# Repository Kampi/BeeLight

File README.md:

# BeeLight - Zigbee based light & environment sensor for Home Automation

## Table of Contents

- [BeeLight - Zigbee based light \& environment sensor for Home Automation](#beelight---zigbee-based-light--environment-sensor-for-home-automation)
  - [Table of Contents](#table-of-contents)
  - [About](#about)
    - [Technical features](#technical-features)
  - [Before you start](#before-you-start)
    - [PCB](#pcb)
    - [Firmware](#firmware)
      - [Build the firmware](#build-the-firmware)
      - [Flash the firmware](#flash-the-firmware)
      - [Generate the production config for the device](#generate-the-production-config-for-the-device)
        - [Using west](#using-west)
        - [Using the command line](#using-the-command-line)
    - [Housing](#housing)
    - [Zigbee](#zigbee)
      - [Standard clusters](#standard-clusters)
      - [Custom cluster](#custom-cluster)
      - [Zigbee Dongle](#zigbee-dongle)
      - [Install the device to Zigbee2MQTT](#install-the-device-to-zigbee2mqtt)
      - [Using the NCS Zigbee Shell](#using-the-ncs-zigbee-shell)
  - [Directory structure](#directory-structure)
  - [Resources](#resources)
  - [Maintainer](#maintainer)

## About

Open-Source Zigbee-based light and environmental sensor with [Zigbee2MQTT](https://www.zigbee2mqtt.io/) support for your Home Automation (e.g., Home Assistant).

### Technical features

- Cutting-edge MCU module with an nRF54L, running Zephyr
- Powered by a single coin cell
- Can measure
  - Temperature
  - Humidity
  - Pressure
  - IAQ
  - CO2 equivalent
  - VOC equivalent
  - Light intensity
  - Battery voltage
- Small housing (40x42x20 mm)
- Very basic electronic → Can be assembled by hand very easily
- Zigbee2MQTT compatibility

## Before you start

The project directory contains the hardware as a [KiCad 9](https://www.kicad.org/download/) project, the firmware and the Zigbee2MQTT configuration. You can check it out with Git:

```sh
git clone https://github.com/Kampi/BeeLight
cd BeeLight
git submodule update --init --recursive
cd firmware/app
west init -l .
west update
```

You also need [nrfutil](https://www.nordicsemi.com/Products/Development-tools/nRF-Util) and the `nrf5sdk-tools` to flash the production configuration to the sensor. First install `nrfutil` and then run the following command to install the SDK tools:

```sh
nrfutil install nrf5sdk-tools
```

### PCB

The project uses [Kibot](https://github.com/INTI-CMNB/KiBot) to automatically generate all required output data. After installing it you can execute the following command to run it:

```sh
cd hardware
./kibot-launch.sh
```

As an alternative you can run it via CI/CD in GitHub.

> **NOTE**
> You have to provide a Mouser API key with a variable called `MOUSER_KEY` to make use of the KiCost feature in the Kibot job.
>
> **NOTE**
> The programming connector is optional and can be left out or unsoldered after flashing the device.

### Firmware

#### Build the firmware

The firmware can be built with the following command:

```sh
cd firmware/app
west build --build-dir build . --pristine --board beelight@1/nrf54l15/cpuapp -- -DNCS_TOOLCHAIN_VERSION=NONE -DEXTRA_CONF_FILE=config/debug.conf -DBOARD_ROOT=.
```

You also need a Zigbee network to test and integrate the device. I use [Zigbee2MQTT](https://www.zigbee2mqtt.io/) running on a Raspberry Pi which allows me to connect my Zigbee network with my Home Automation.

> **NOTE**
> I do not support other Zigbee networks (like [ZHA](https://www.home-assistant.io/integrations/zha/)). The Zigbee standard allows you to connect the device with all other networks but I can't deliver a functional integration for these networks. You have to do it on your own!

#### Flash the firmware

After building the firmware you can run

```sh
west flash
```

to flash the firmware into the module.

> **NOTE**
> For some reason the current consumption stays high after flashing. I recommend a complete power cycle after flashing to make sure the device is consuming the lowest current possible.

#### Generate the production config for the device

##### Using west

You can run the command `west upload_config` to build and upload your configuration to the device automatically.

##### Using the command line

You must flash a production config to the device, before you can use it with Zigbee. You can either use the prebuilt config from the project or adjust it according to your needs.

```sh
nrfutil nrf5sdk-tools zigbee production_config zigbee_config.yml zigbee_config.hex --offset 0x17a000
nrfjprog --program zigbee_config.hex --verify
```

> **NOTE**
> The offset `0x17a000` is taken from the `PM_ZBOSS_PRODUCT_CONFIG_OFFSET` macro in `build/<app>/zephyr/include/generated/pm_config.h`. Also make sure to change `extended_address` in the Zigbee
> configuration file if you use more than one device!

### Housing

The housing is optimized for 3D printing and needs ~12 g of filament (PLA). You can find all the needed files in the `3d-printing` directory of this project.

### Zigbee

The device uses different standard and custom cluster to report the data to the network.

#### Standard clusters

| Cluster | ID |
| ------- | -- |
| Temperature | 0x0402 |
| Pressure | 0x0403 |
| Rel. Humidity | 0x0405 |
| Light | 0x0400 |

#### Custom cluster

The device uses three custom cluster to report `IAQ`, `VOC` and `CO2` to the network. Both clusters have three attributes for `value`, `min_value`, `max_value` and `tolerance`.

| Cluster | ID |
| ------- | -- |
| IAQ | 0x1A0A |
| VOC | 0x1A0B |
| CO2 | 0x1A0C |

| Attribute | ID |
| --------- | -- |
| Value | 0x0000 |
| Min. Value | 0x0001 |
| Max. Value | 0x0002 |
| Tolerance | 0x0003 |

#### Zigbee Dongle

Make sure to use a Zigbee 3 compatible dongle like [SONOFF ZBDongle-E](https://sonoff.tech/product/gateway-and-sensors/sonoff-zigbee-3-0-usb-dongle-plus-e/) and update the firmware to the latest version to prevent issues. You can follow [this](https://dongle.sonoff.tech/sonoff-dongle-flasher/) guide if you use a SONOFF dongle.

#### Install the device to Zigbee2MQTT

> **NOTE**
> Because it's not possible to use custom clusters with Zigbee2MQTT easily, you must adjust the application directly to use the sensor. Please take a look into the directory `z2m/data/external_converters/example` if you want to check how the modified files look like.

1. Download and install [Zigbee2MQTT](https://github.com/zigbee2mqtt/hassio-zigbee2mqtt)
2. Copy the external converter from `z2m/data_external_converters` to the `data` directory of your `Zigbee2MQTT` installation
3. Switch into the directory `.../zigbee2mqtt/node_modules/zigbee-herdsman/dist/zspec/zcl/definition` and open `cluster.js` and add the following code to `exports.Clusters`

```ts
...
    msBeelightIAQ: {
        ID: 6666,
        attributes: {
            measuredValue: { ID: 0, type: enums_1.DataType.UINT16 },
            minMeasuredValue: { ID: 1, type: enums_1.DataType.UINT16 },
            maxMeasuredValue: { ID: 2, type: enums_1.DataType.UINT16 },
            tolerance: { ID: 3, type: enums_1.DataType.UINT8 },
        },
        commands: {},
        commandsResponse: {},
    },
    msBeelightVOC: {
        ID: 6667,
        attributes: {
            measuredValue: { ID: 0, type: enums_1.DataType.UINT16 },
            minMeasuredValue: { ID: 1, type: enums_1.DataType.UINT16 },
            maxMeasuredValue: { ID: 2, type: enums_1.DataType.UINT16 },
            tolerance: { ID: 3, type: enums_1.DataType.UINT8 },
        },
        commands: {},
        commandsResponse: {},
    },
    msBeelightCO2: {
        ID: 6668,
        attributes: {
            measuredValue: { ID: 0, type: enums_1.DataType.UINT16 },
            minMeasuredValue: { ID: 1, type: enums_1.DataType.UINT16 },
            maxMeasuredValue: { ID: 2, type: enums_1.DataType.UINT16 },
            tolerance: { ID: 3, type: enums_1.DataType.UINT8 },
        },
        commands: {},
        commandsResponse: {},
    },
...
```

4. Save the file
5. Switch to `.../zigbee2mqtt/node_modules/zigbee-herdsman-converters/dist/lib`
6. Open the file `modernExtend.js` and add the following cluster to the end of the list at the end of the file:
7. Add

```js
...
exports.BeeLight_iaq = BeeLight_iaq;
exports.BeeLight_co2 = BeeLight_co2;
exports.BeeLight_voc = BeeLight_voc;
...
```

8. Extend the following section

```js
// #region Measurement and Sensing
function BeeLight_iaq(args = {}) {
    return numeric({
        name: "BeeLight_iaq",
        cluster: "msBeelightIAQ",
        attribute: "measuredValue",
        reporting: { min: "5_MINUTES", max: "1_HOUR", change: 10 },
        description: "Measured IAQ value",
        unit: "",
        scale: 1,
        access: "STATE_GET",
        ...args,
    });
}
function BeeLight_co2(args = {}) {
    return numeric({
        name: "BeeLight_co2",
        cluster: "msBeelightCO2",
        attribute: "measuredValue",
        reporting: { min: "5_MINUTES", max: "1_HOUR", change: 10 },
        description: "Measured CO2 value",
        unit: "ppm",
        scale: 1,
        access: "STATE_GET",
        ...args,
    });
}
function BeeLight_voc(args = {}) {
    return numeric({
        name: "BeeLight_voc",
        cluster: "msBeelightVOC",
        attribute: "measuredValue",
        reporting: { min: "5_MINUTES", max: "1_HOUR", change: 10 },
        description: "Measured VOC value",
        unit: "ppm",
        scale: 1,
        access: "STATE_GET",
        ...args,
    });
}
...
```

9. Save the file
10. Restart Zigbee2MQTT

The device can now be connected to your Zigbee network and with this to your Home Assistant.

#### Using the NCS Zigbee Shell

You can test the device by using the NCS Zigbee Shell example and an nRF54DK or an nRF5340DK.

1. Flash the Zigbee Shell example to your board
2. Execute `nvram disable`
3. Execute `bdb role zc`
4. Execute `bdb channel 11`
5. Execute `bdb start`
6. Flash the sensor device firmware and the network configuration
7. Reset the sensor device and start the join procedure
8. You should get this output from the network coordinator device

```sh
[00:05:05.648,345] <inf> zigbee_app_utils: Joined network successfully (Extended PAN ID: f4ce36b2d4c06ca0, PAN ID: 0x6057)
[00:05:24.536,529] <inf> zigbee_app_utils: Device authorization event received (short: 0x02fa, long: 86d79ac5bae41fa3, authorization type: 3, authorization status: 0)
[00:05:24.536,773] <inf> zigbee_app_utils: Unimplemented signal (signal: 53, status: 0)
[00:05:24.537,139] <inf> zigbee_app_utils: Device update received (short: 0x02fa, long: 86d79ac5bae41fa3, status: 1)
```

9. Now you can read the clusters with `zcl attr read <Address> 10 <Cluster> 0x0104 0x0000`
10. Use `zcl subscribe on <Address> 10 <Cluster> 0x0104 0x00 33 <Min (s)> <Max (s)>` to create a binding for the given cluster

## Directory structure

- `3d-print`: All 3D print-related files
- `cad`: All relevant 3D models
- `docs`: All kinds of project documentation like schematics, BOM, etc.
  - `drawings`: 2D drawings for subcomponents, etc.
  - `images`: All documentation-relateBd images
- `hardware`: KiCad project for the PCB
- `firmware`: Zephyr project for the device firmware
- `prebuilt`: Prebuilt binaries
- `z2m`: Zigbee2MQTT-related files

## Resources

- [Adding new Zigbee2MQTT devices](https://www.zigbee2mqtt.io/advanced/support-new-devices/01_support_new_devices.html)
- [Zigbee Cluster Library Specification](https://zigbeealliance.org/wp-content/uploads/2019/12/07-5123-06-zigbee-cluster-library-specification.pdf)
- [Generating HEX files for Zigbee production configuration](https://docs.nordicsemi.com/bundle/nrfutil/page/nrfutil-nrf5sdk-tools/guides/generating_zigbee_hex.html)
- [Zigbee Converters](https://github.com/Koenkk/zigbee-herdsman-converters)
- [KiBot Template](https://github.com/nguyen-v/KDT_Hierarchical_KiBot)
- [Zigbee Shell](https://docs.nordicsemi.com/bundle/addon-zigbee-r23-latest/page/lib/shell.html#zdo_ieeeaddr)

## Maintainer

- [Daniel Kampert](mailto:DanielKampert@kampis-elektroecke.de)

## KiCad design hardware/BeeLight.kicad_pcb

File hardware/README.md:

<h1 align="center">Template</h1>

<p align="center" width="100%">
  
</p>

***

<p align="center">
  
&nbsp; &nbsp; &nbsp; &nbsp;
  
</p>

***

## SPECIFICATIONS

| Parameter | Value |
| --- | --- |
| Dimensions | 32.0 × 24.0 mm |

***

## DIRECTORY STRUCTURE

    .
    ├─ Computations       # Misc calculations
    ├─ HTML               # HTML files for generated webpage
    ├─ Images             # Pictures and renders
    │
    ├─ kibot_resources    # External resources for KiBot
    │  ├─ colors          # Color theme for KiCad
    │  ├─ fonts           # Fonts used in the project
    │  ├─ scripts         # External scripts used with KiBot
    │  └─ templates       # Templates for KiBot generated reports
    │
    ├─ kibot_yaml         # KiBot YAML config files
    ├─ KiRI               # KiRI (PCB diff viewer) files
    │
    ├─ lib                # KiCad footprint and symbol libraries
    │  ├─ 3d_models       # Component 3D models
    │  ├─ lib_fp          # Footprint libraries
    │  └─ lib_sym         # Symbol libraries
    │
    ├─ Logos              # Logos
    │
    ├─ Manufacturing      # Assembly and fabrication documents
    │  ├─ Assembly        # Assembly documents (BoM, pos, notes)
    │  │
    │  └─ Fabrication     # Fabrication documents (ZIP, notes)
    │     ├─ Drill Tables # CSV drill tables
    │     └─ Gerbers      # Gerbers
    │
    ├─ Report             # Reports for ERC/DRC
    ├─ Schematic          # PDF of schematic
    ├─ Templates          # Title block templates
    ├─ Testing
    │  └─ Testpoints      # Testpoints tables
    │
    └─ Variants           # Outputs for assembly variants

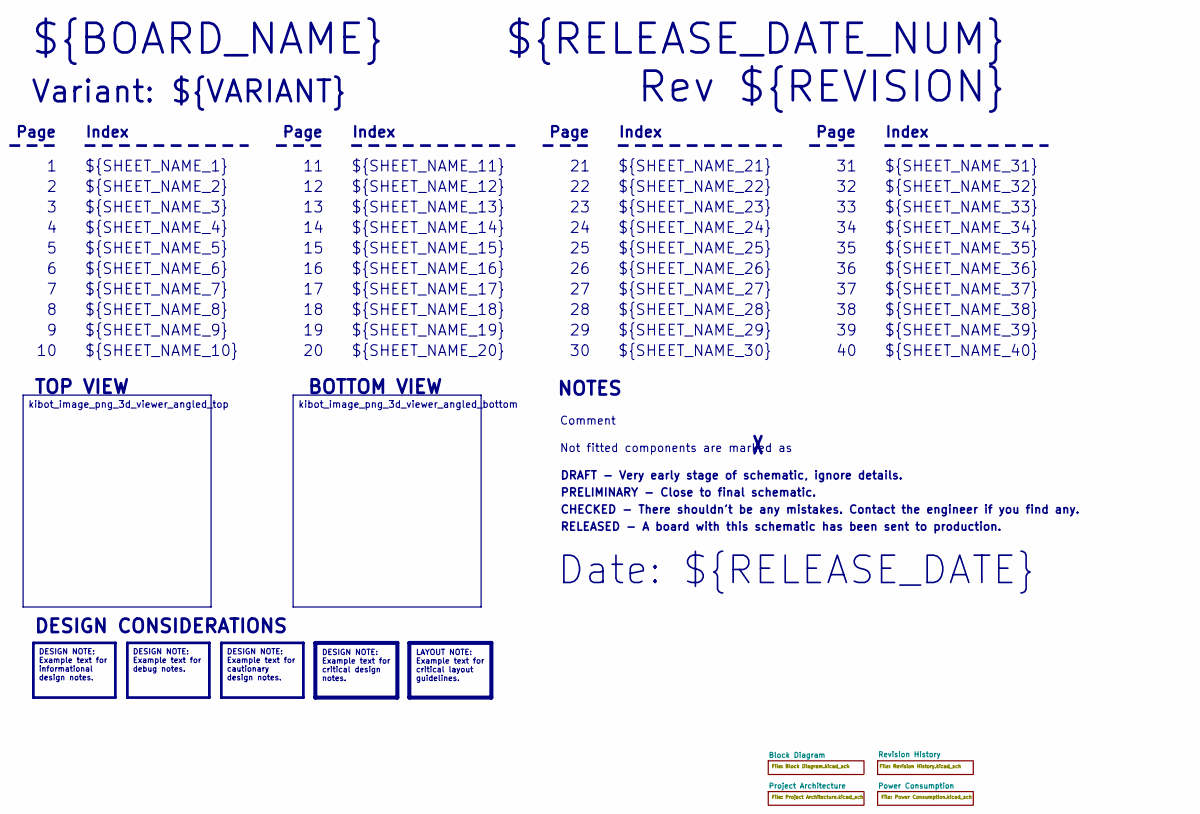
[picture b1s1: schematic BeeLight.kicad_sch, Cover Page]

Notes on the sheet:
Variant: ${VARIANT}
RELEASED - A board with this schematic has been sent to production.
${SHEET_NAME_24}
Index
Page
PRELIMINARY - Close to final schematic.
${SHEET_NAME_22}
DRAFT - Very early stage of schematic, ignore details.
${SHEET_NAME_12}
${SHEET_NAME_8}
${SHEET_NAME_2}
${SHEET_NAME_5}
${SHEET_NAME_20}
${SHEET_NAME_23}
${RELEASE_DATE_NUM}
${SHEET_NAME_35}
Not fitted components are marked as
${SHEET_NAME_11}
${SHEET_NAME_6}
${SHEET_NAME_37}
${SHEET_NAME_26}
${SHEET_NAME_36}
Rev ${REVISION}
${SHEET_NAME_15}
CHECKED - There shouldn't be any mistakes. Contact the engineer if you find any.
BOTTOM VIEW
${SHEET_NAME_14}
${SHEET_NAME_21}
${SHEET_NAME_17}
${SHEET_NAME_18}
Date: ${RELEASE_DATE}
${SHEET_NAME_7}
${SHEET_NAME_31}
${BOARD_NAME}
NOTES
${SHEET_NAME_40}
${SHEET_NAME_39}
${SHEET_NAME_32}
${SHEET_NAME_1}
${SHEET_NAME_9}

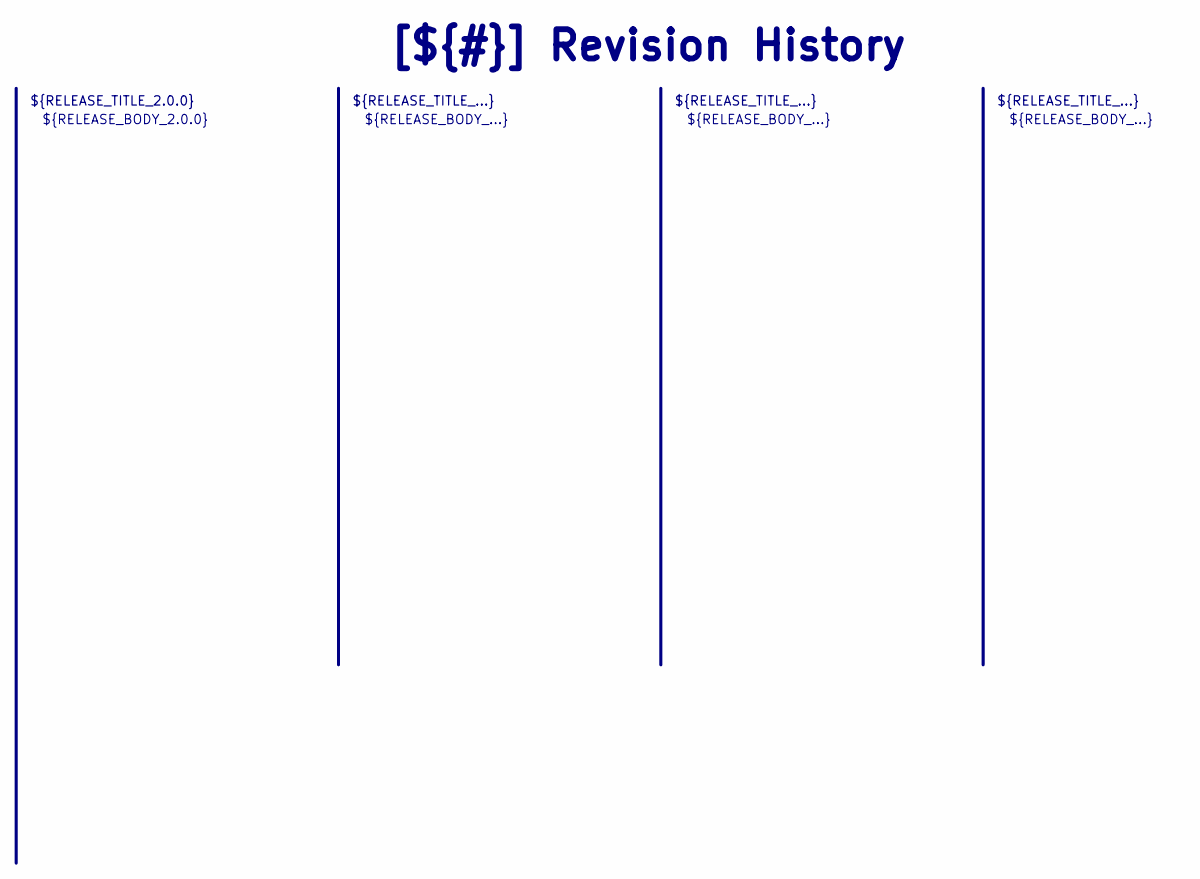
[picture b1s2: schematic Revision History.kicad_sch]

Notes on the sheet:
${RELEASE_BODY_...}
[${#}] ${TITLE}
${RELEASE_BODY_2.0.0}
${RELEASE_TITLE_...}
${RELEASE_TITLE_2.0.0}

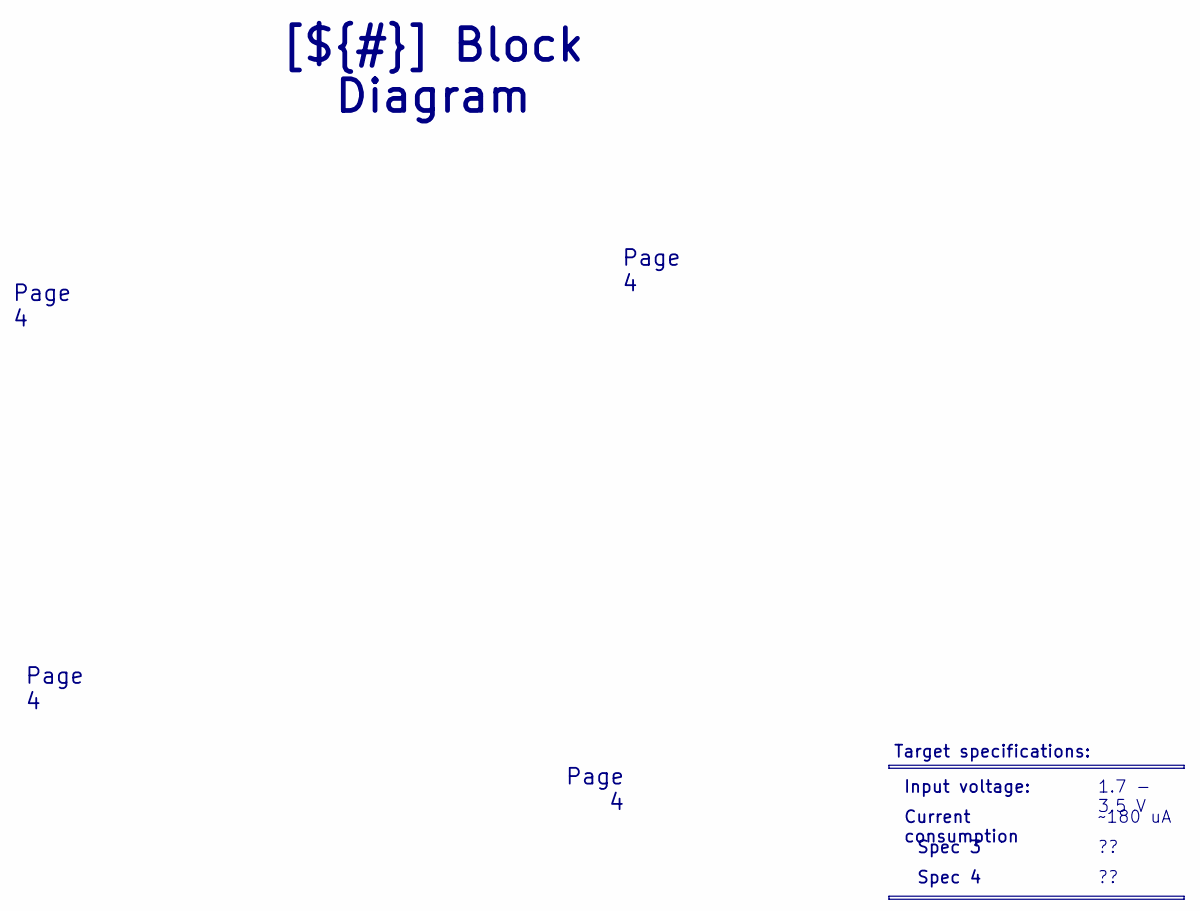
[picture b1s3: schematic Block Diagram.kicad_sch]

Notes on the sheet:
Spec 4
1.7 - 3.5 V
Page 4
[${#}] ${TITLE}
~180 uA
Input voltage:
Target specifications:
Spec 3
Current consumption

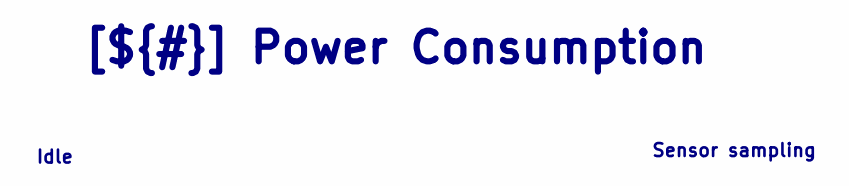
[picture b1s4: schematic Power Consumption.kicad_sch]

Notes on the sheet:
Sensor sampling
[${#}] ${TITLE}
Idle

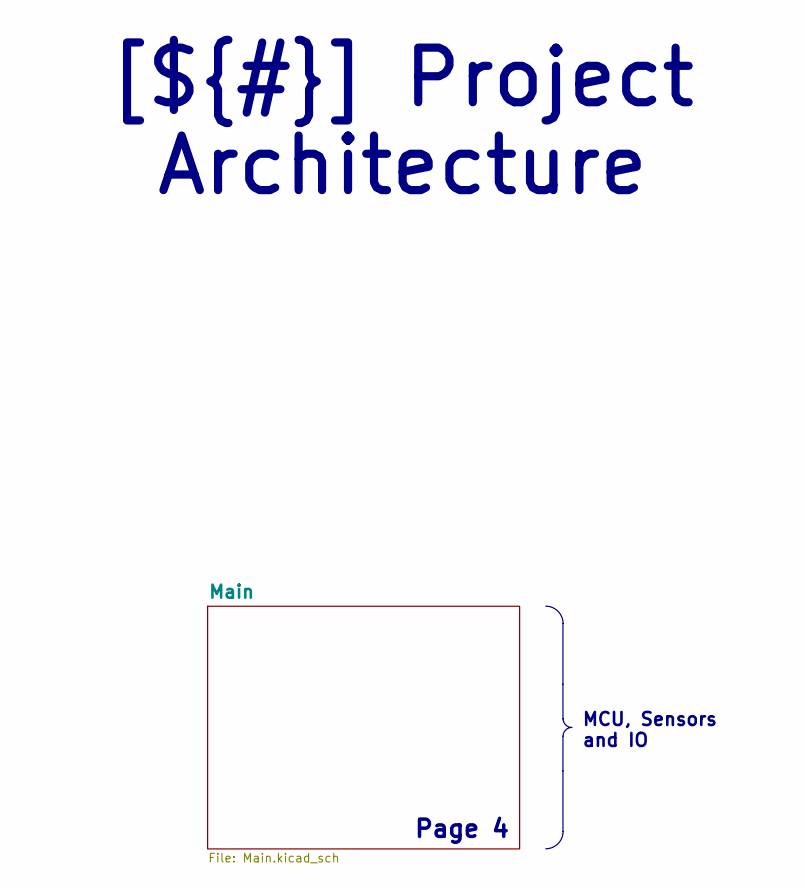
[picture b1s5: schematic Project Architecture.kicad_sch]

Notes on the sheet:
Page 4
MCU, Sensors and IO
[${#}] ${TITLE}

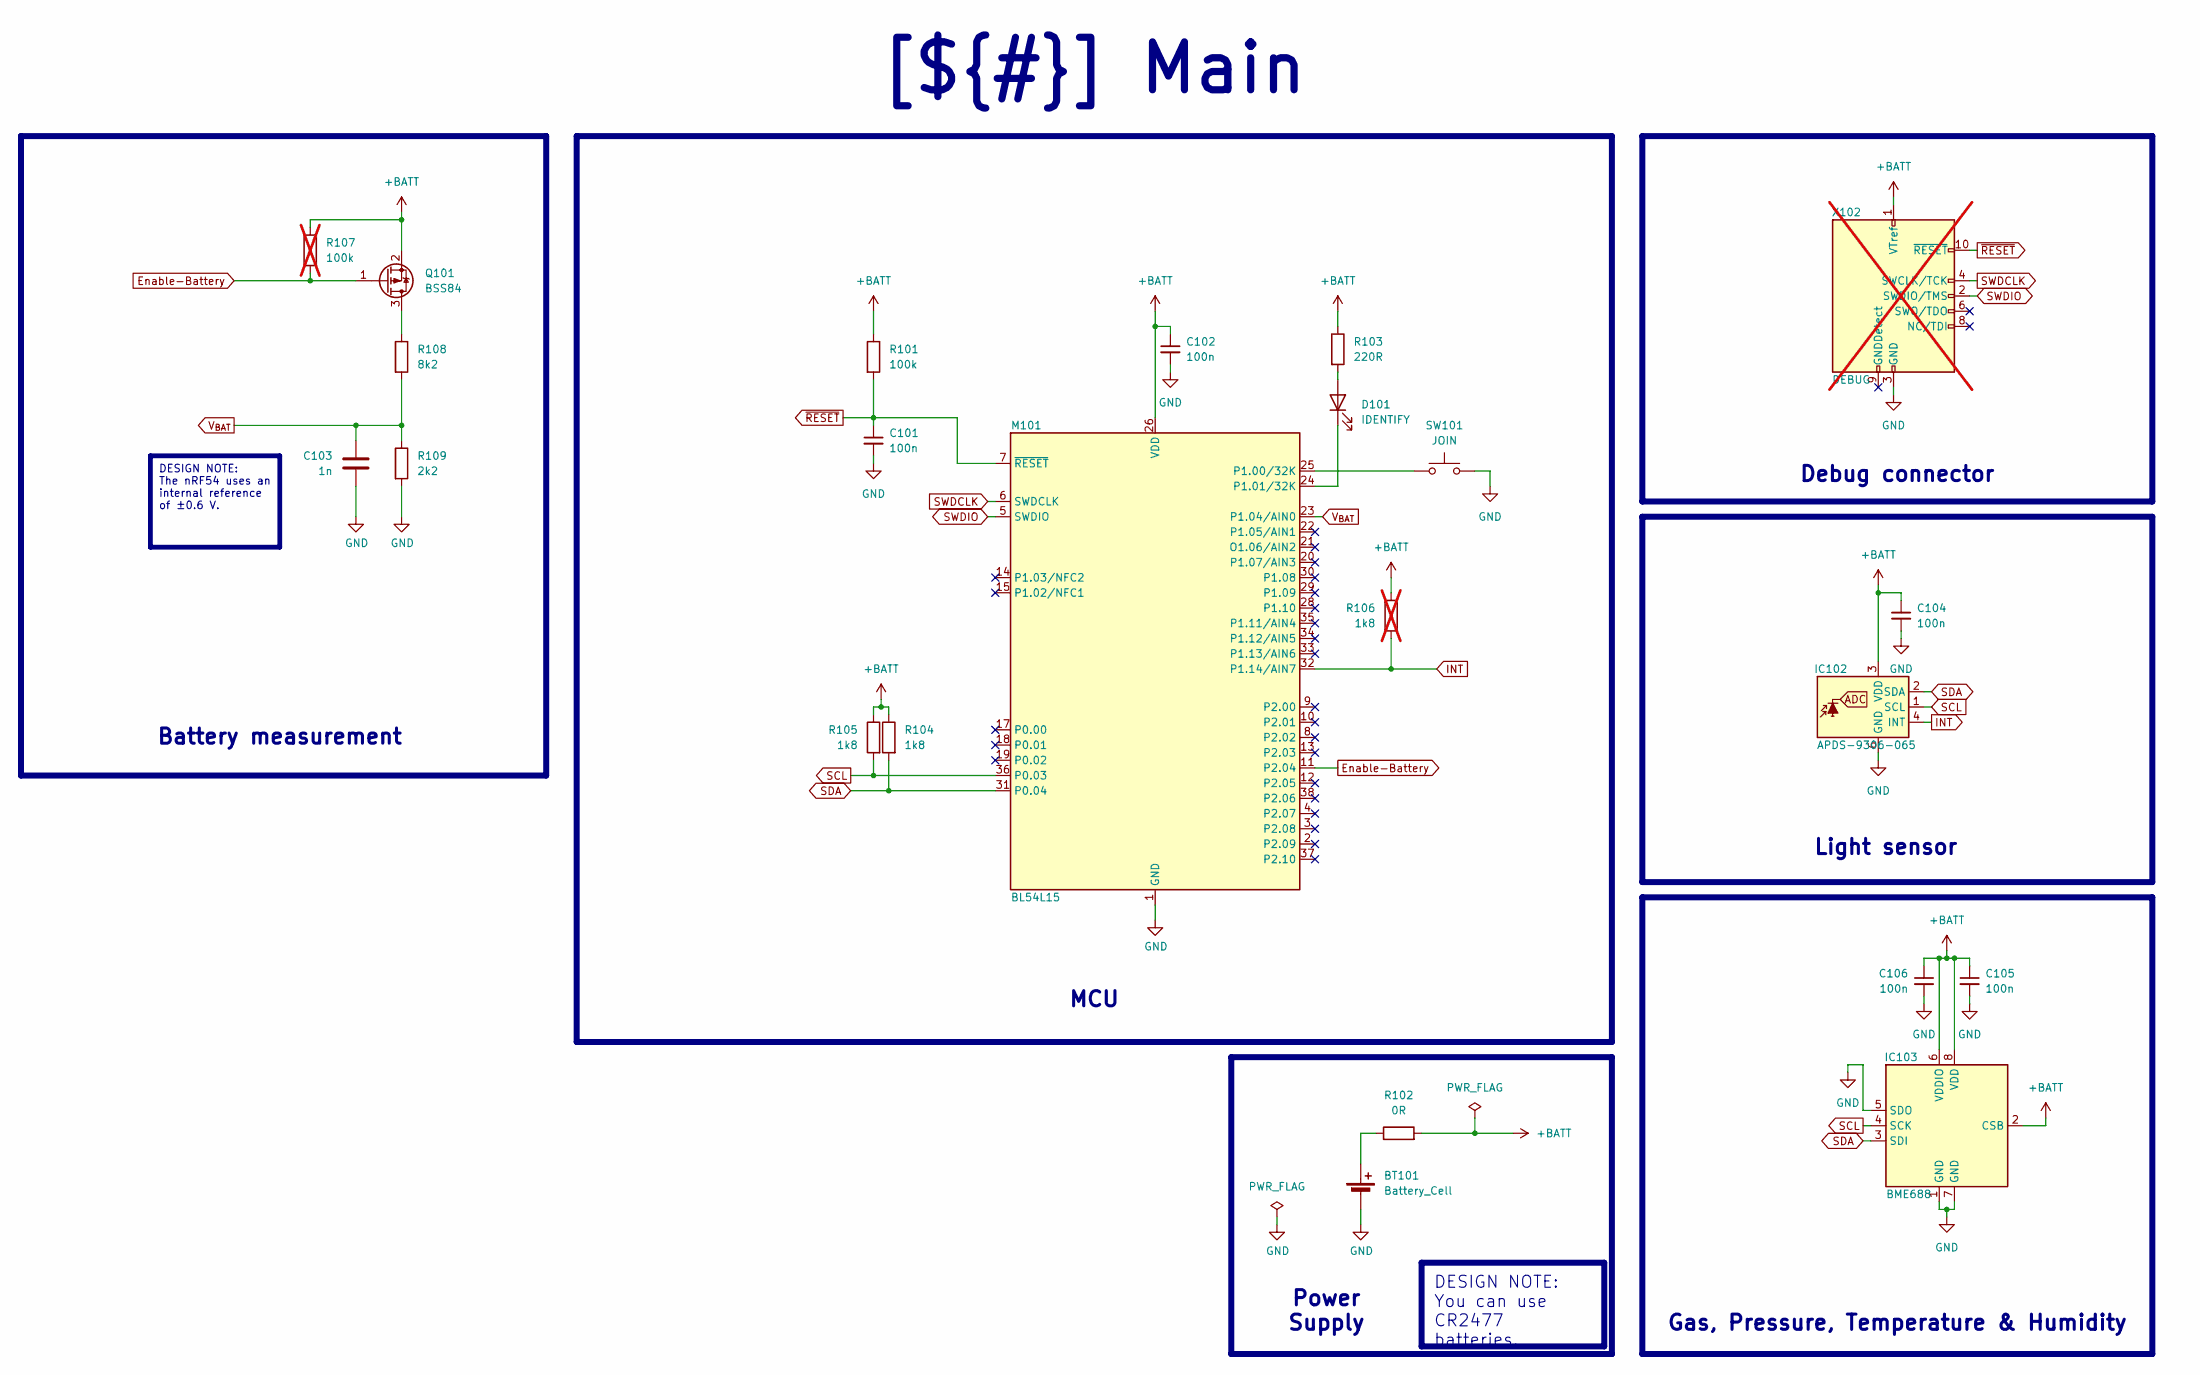
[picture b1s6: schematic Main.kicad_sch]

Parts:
BT101: Battery_Cell; 3039; mouser# 534-3039
C101, C102, C104, C105, C106: 100n; C_0402_1005Metric_Pad0.74x0.62mm_HandSolder; mouser# 581-04025C104KAT4A
C103: 1n; C_0402_1005Metric_Pad0.74x0.62mm_HandSolder; mouser# 81-GCM1555C2A102JE02D
D101: IDENTIFY; LED_0805_2012Metric_Pad1.15x1.40mm_HandSolder; mouser# 630-HSMQ-C170-T0000
IC102: APDS-9306-065; Broadcom_DFN-6_2x2mm_P0.65mm; mouser# 630-APDS-9306-065
IC103: BME688; Bosch_LGA-8_3x3mm_P0.8mm_ClockwisePinNumbering; mouser# 262-BME688
M101: BL54L15; mouser# 239-453-00001C
Q101: BSS84; SOT-23-3; mouser# 512-BSS84
R101: 100k; R_0402_1005Metric_Pad0.72x0.64mm_HandSolder; mouser# 603-RC0402FR-07100KL
R102: 0R; R_0805_2012Metric_Pad1.20x1.40mm_HandSolder; mouser# 652-CR0805AJ/-000EAS
R103: 220R; R_0402_1005Metric_Pad0.72x0.64mm_HandSolder; mouser# 652-CR0402-JW-221GLF
R104, R105: 1k8; R_0402_1005Metric_Pad0.72x0.64mm_HandSolder; mouser# 603-RC0402FR-071K8L
R106: 1k8; R_0402_1005Metric_Pad0.72x0.64mm_HandSolder; mouser# 603-RC0402FR-071K8L; not fitted
R107: 100k; R_0402_1005Metric_Pad0.72x0.64mm_HandSolder; mouser# 603-RC0402FR-07100KL; not fitted
R108: 8k2; R_0402_1005Metric_Pad0.72x0.64mm_HandSolder; mouser# 603-RT0402BRD078K2L
R109: 2k2; R_0402_1005Metric_Pad0.72x0.64mm_HandSolder; mouser# 603-RT0402BRD072K2L
SW101: JOIN; WS-TASV-6x6; mouser# 710-430182095816
X102: DEBUG; PinHeader_2x05_P1.27mm_Vertical; mouser# 200-SHF-105-01-L-D-TH-TR; not fitted

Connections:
+BATT: C102.1, C104.1, C105.1, C106.1, IC102.3 (VDD), IC103.2 (CSB), IC103.6 (VDDIO), IC103.8 (VDD), M101.26 (VDD), Q101.2 (S), R101.1, R102.2, R103.1, R104.1, R105.1, R106.1, R107.1, X102.1 (VTref)
Enable-Battery: M101.11 (P2.04), Q101.1 (G), R107.2
GND: BT101.2 (-), C101.2, C102.2, C103.2, C104.2, C105.2, C106.2, IC102.6 (GND), IC103.1 (GND), IC103.5 (SDO), IC103.7 (GND), M101.1 (GND), M101.16 (GND), M101.27 (GND), M101.39 (GND), R109.2, SW101.1, X102.3 (GND), X102.5 (GND)
INT: IC102.4 (INT), M101.32 (P1.14/AIN7), R106.2
unnamed: BT101.1 (+), R102.1
unnamed: D101.2 (A), R103.2
unnamed: D101.1 (K), M101.24 (P1.01/32K)
unnamed: M101.25 (P1.00/32K), SW101.2
unnamed: Q101.3 (D), R108.1
SCL: IC102.1 (SCL), IC103.4 (SCK), M101.36 (P0.03), R105.2
SDA: IC102.2 (SDA), IC103.3 (SDI), M101.31 (P0.04), R104.2
SWDCLK: M101.6 (SWDCLK), X102.4 (SWCLK/TCK)
SWDIO: M101.5 (SWDIO), X102.2 (SWDIO/TMS)
V_{BAT}: C103.1, M101.23 (P1.04/AIN0), R108.2, R109.1
~RESET: C101.1, M101.7 (~RESET), R101.2, X102.10 (~RESET)

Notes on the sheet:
DESIGN NOTE: You can use CR2477 batteries.
[${#}] ${TITLE}
Power Supply
Battery measurement
MCU
Light sensor
Debug connector
DESIGN NOTE: The nRF54 uses an internal reference of ±0.6 V.
Gas, Pressure, Temperature & Humidity

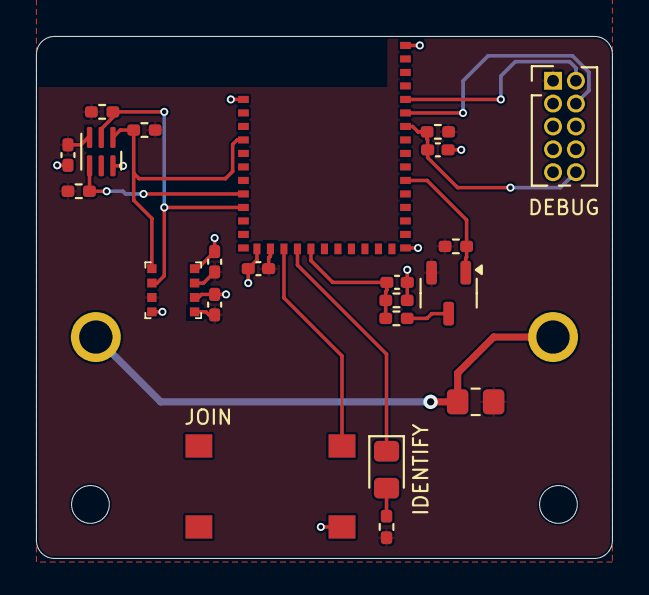
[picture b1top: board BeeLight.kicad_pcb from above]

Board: 2 copper layers, 32.0 x 29.0 mm, 23 parts (1 on the bottom side), 15 nets.

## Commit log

2024-12-15 Initialize repository
2024-12-31 Working on revision 1.0
2025-01-12 Firmware is compiling with custom board, testing first hardware release
2025-01-15 - Replace nRF53 with nRF54L - Working on version 2 with BME688
2025-01-19 Working on firmware
2025-01-19 Update ZigBee2MQTT definition, housing and the device image
2025-02-05 Add offer from PCBWay for Hackster challenge (nRF54 is missing because not available)
2025-03-18 Switch to BM15C module
2025-04-10 Replace nRF54 module
2025-05-04 Started with port to NCS 3.0.0 with ncs-zigbee and nRF54
2025-05-12 Hardware rev 1 seems to be working
2025-05-12 Update documentation
2025-05-12 Firmware is working for nRF54, Zigbee is still open
2025-05-26 Hardware is completely functional, add missing mounting holes
2025-05-26 Firmware is functional on nRF54L15
2025-05-27 Working on Zigbee interface
2025-05-28 Add dimension to PCB specification Kibot output
2025-05-28 Create 'other' directory with Kibot
2025-06-01 Update documentation, add binding to Z2M config, firmware can set sample time via Kconfig now
2025-06-04 - Fix typos in DTS includes - Fix wrong patch command - Add blocklist to west.yml
2025-06-15 Bring up hardware and firmware
    - Remove old files
    - Update README.md
    - Update converter for z2m
    - Fix typos in DTS includes
    - Fix wrong patch command
    - Add dimension to PCB specification Kibot output
2025-06-18 - Remove old files
    - Replace nRF54 module
    - Update README.md
    - Update converter for z2m
    - Fix typos in DTS includes
    - Fix wrong patch command
    - Add BME688
2025-06-18 Implement new CI/CD workflow
2025-06-18 Working on revision 2.0
    - Remove old files
    - Replace nRF53 with nRF54L15
    - Update README.md
    - Update converter for z2m
    - Fix typos in DTS includes
    - Fix wrong patch command
2025-06-19 Add CI/CD for firmware
2025-06-19 Add housing version 22
2025-06-19 Add CI/CD pipeline for Zigbee configuration
2025-06-19 Update Outputs
2025-06-22 Fix wrong VBAT signal
2025-06-27 - Change ADC filter capacitor to 1 nF - Update documentation with current consumption - Update CI/CD pipeline
2025-06-27 Update CI/CD pipeline
2025-06-27 Optimizing power consumption (40 uA with sensors and Zigbee)
2025-06-28 Add BOM generation for Mouser BOM tool
2025-06-28 Add Device Tree overlay for revision 2 hardware
2025-06-29 Add KiCost
2025-07-13 Working on revision 2.0
    Working on revision 2.0
    - Remove old files
    - Replace nRF53 with nRF54L15
    - Update README.md
    - Update converter for z2m
    - Update documentation
2025-07-14 Clean up repository
2025-07-21 Push outputs from CI/CD (2025-07-21 23:08:18)
2025-07-23 Update pcb.yaml
    Remove log files from artifacts
2025-09-09 Issue #40, Issue #42
2025-10-07 Backlink to CADLAB.io has been added.
2025-10-07 Some weird errors
2025-10-13 Working on revision 2.0
    - Remove old files
    - Remove log files from artifacts
    - Replace nRF53 with nRF54L15
    - Update README.md
    - Update converter for z2m
    - Update documentation
2025-10-13 Issue #40, Issue #42, Issue #45
2025-10-14 Task: Update documentation
    - Simplify BeeLight headers
    - Add group-filter to west manifest
    - Add commit template
2025-10-14 Firmware: Add AStyle support for west
2025-10-14 Device Tree: Fix I2C issues - Remove GPIO I2C from rev 2 device tree - Fix wrong pinctrl references for I2C2
2025-10-14 Code clean up
2025-10-14 Fix wrong KiBot version variables
2025-10-15 Add configuration settings for Coderabbit integration
2025-10-20 - Fix wrong KiBot version variables - CI/CD: Add CodeRabbit configuration file - CI/CD: Fix issues reported by CodeRabbit
2025-10-20 Feature: Issue #28
    - Switch from CR2032 to CR2477 batteries for longer runtime
    Closes #28
2025-11-07 - Update CHANGELOG - Update README - Add release or debug info to Zigbee FW version - Fixes from CodeRabbit - Simplify the cluster definitions and rename them
2025-11-10 Bug: Issue #48
    - Wrong date variable in PCB CI/CD
    Closes #48
2025-11-10 Add missing 'Closes' to commit message template
2026-03-02 Update KiBot configuration to the latest version
2026-03-03 Update CI/CD workflow to use environment date
2026-03-17 Zigbee fixes
2026-03-17 Push outputs from CI/CD (2026-03-17 20:23:36)
2026-03-17 Task: Issue #49
    - Update z2m configuration files to latest format
    Closes #49
2026-03-27 Prepare release 2.1
2026-03-27 Push outputs from CI/CD (2026-03-27 07:22:00)
2026-03-27 Push outputs from CI/CD (2026-03-27 07:58:02)
2026-03-27 Add release workflow
2026-03-28 Push outputs from CI/CD (2026-03-28 12:05:06)
2026-03-29 Fix documentation link in README.md

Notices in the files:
README.md:
License: GPL 3.0
